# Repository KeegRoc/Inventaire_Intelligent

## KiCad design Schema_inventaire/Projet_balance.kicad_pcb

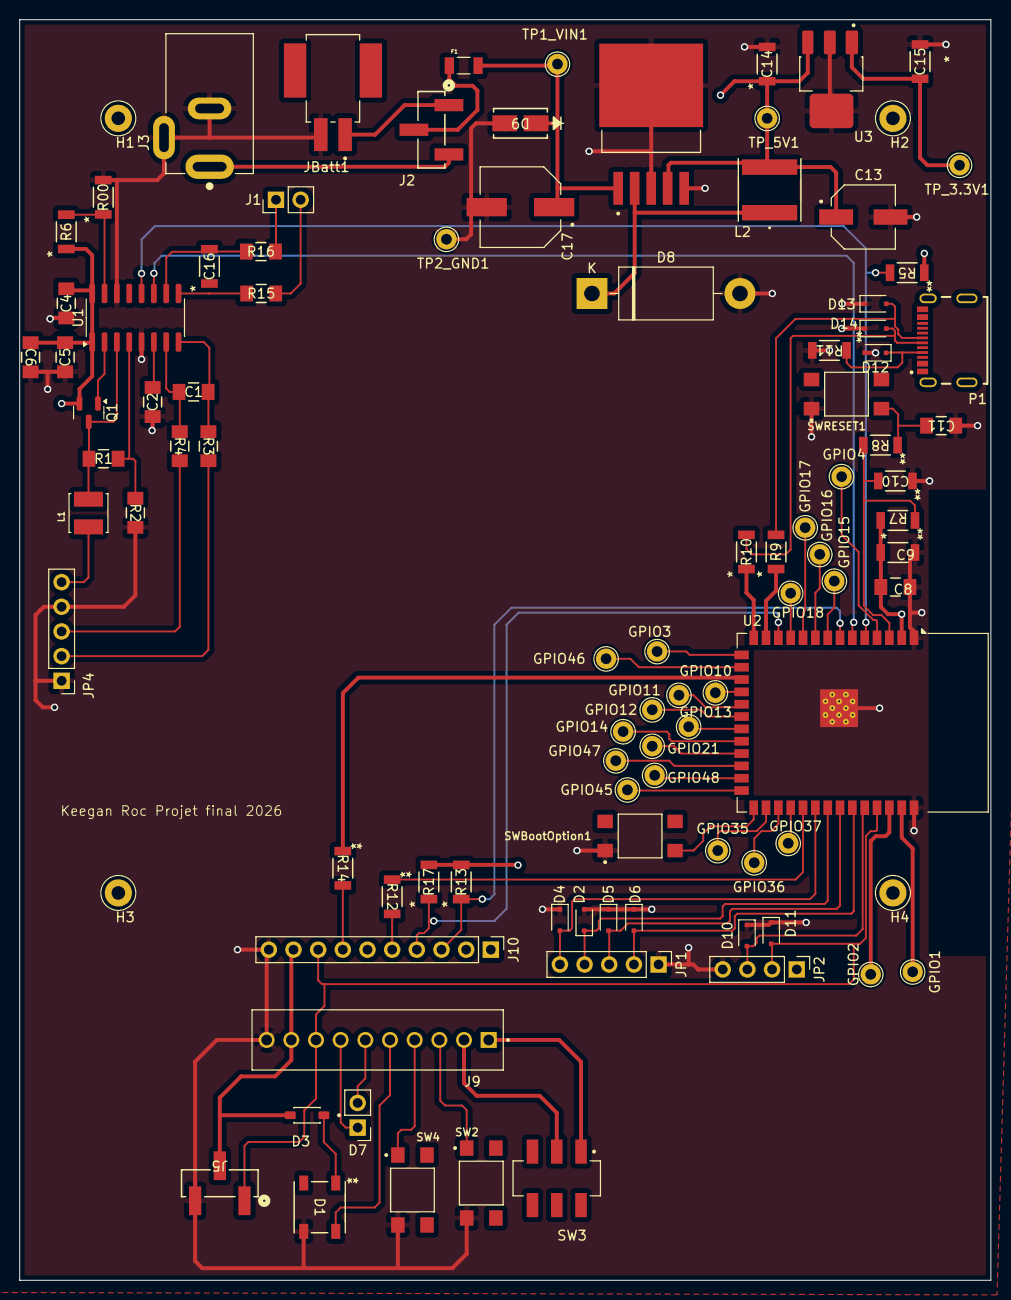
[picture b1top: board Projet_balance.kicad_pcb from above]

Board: 4 copper layers, 100.0 x 129.8 mm, 99 parts (0 on the bottom side), 73 nets.

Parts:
C1, C2, C4, C5, C8, C11: 0.1uF; RC1206N_YAG-M
C6: 10uF; RC1206N_YAG-M
C9: 22uF; 1206LSeries_LTF-M
C10, C14: 1uF; 1206LSeries_LTF-M
C13: 220uF; CAP_16SVPK220M
C15: 4.7uF; 1206LSeries_LTF-M
C16: 0.1uF; 1206LSeries_LTF-M
C17: 680uF; CAP_16SVPK680M
D1: WS2812B; COM-16347_SPK-M
D2, D4, D5, D6, D10, D11, D12, D13, D14: Diode_SMD:D_SOD-323F; D_SOD-323F
D3: 1N4148; SOD3716X135N
D7: LED_SET; PinHeader_1x02_P2.54mm_Vertical
D8: 1N5824; D_DO-201AD_P15.24mm_Horizontal
D9: PTVS5V0Z1USK; SMASeries_LTF-M
F1: Fuse; Resistance 1206
GPIO1, GPIO2, GPIO3, GPIO4, GPIO10, GPIO11, GPIO12, GPIO13, GPIO14, GPIO15, GPIO16, GPIO17, GPIO18, GPIO21, GPIO35, GPIO36, GPIO37, GPIO45, GPIO46, GPIO47, GPIO48: TestPoint; test_point_proto2
H1, H2, H3, H4: MountingHole_Pad_MP; TestPoint_Loop_D3.50mm_Drill1.4mm_Beaded
J1: Conn_01x02; PinHeader_1x02_P2.54mm_Vertical
J2: Jumper; CONN03_87898_M-5p84_MOL
J3: Power jack 9V; CUI_PJ-002A
J5: LCD; CONN03_87898_M-5p84_MOL
J9: Conn_01x10; PHOENIX_1725737
J10: Conn_01x10; PinHeader_1x10_P2.54mm_Vertical
JBatt1: Batt; PHOENIX_1702473
JP1: JTAG; PinHeader_1x05_P2.54mm_Vertical
JP2: UART; PinHeader_1x04_P2.54mm_Vertical
JP4: Conn_01x05; PinHeader_1x05_P2.54mm_Vertical
L1: 3.3uH; IND_LQH44PN3R3MP0K
L2: 33uH; IND_TAIYO_NRS6028_TAY
P1: USB_C_Plug_USB2.0; GCT_USB4215-03-A_REVA
Q1: MMBTA56; SOT-23
R00, R8, R9, R10: 0; 1206LSeries_LTF-M
R1: 20k; RC1206N_YAG-M
R2: 8.2k; RC1206N_YAG-M
R3, R4, R15, R16: 100; RC1206N_YAG-M
R5: 4.7k; 1206LSeries_LTF-M
R6, R7, R13, R17: 10k; 1206LSeries_LTF-M
R11: 5.1k; 1206LSeries_LTF-M
R12: 22; 1206LSeries_LTF-M
R14: 220; 1206LSeries_LTF-M
SW2: SW_SEL; SW_TL3305AF260QG
SW3: On/Off; SW_JS202011SCQN
SW4: SW_OPT; SW_TL3305AF260QG
SWBootOption1: SW_Push; SW_TL3305AF260QG
SWRESET1: SW_Push; SW_TL3305AF260QG
TP1_VIN1, TP2_GND1: TestPoint; test_point_proto2
TP_3.3V1, TP_5V1: TestPoint; test_point_proto2
U1: HX711; SOP-16_3.9x9.9mm_P1.27mm
U2: ESP32-S3-WROOM-1
U3: LDL1117S33R; SOT230P700X180-4N
U5: LM2575-5.0BU; VREG_TPS79625KTTR

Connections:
5V: C13.1, C14.1, D3.2 (A), J5.2, J9.9, J10.6, J10.9, L2.2, U3.3 (VI), U5.4 (FB)
+3.3V: C4.2, C5.2, C6.1, C8.1, C9.1, C15.1, JP2.1, Q1.2 (E), R5.1, R6.1, R7.2, R13.2, R17.2, TP_3.3V1.1, U1.1 (VSUP), U1.16 (DVDD), U2.2 (3V3), U3.1 (VO)
/Microcontrôleur/EN: C10.2, R7.1, R8.2, U2.3 (EN)
/Microcontrôleur/I0O: SWBootOption1.2, U2.27 (IO0)
/Microcontrôleur/LED_ON-: R14.1, U2.17 (IO9)
/Microcontrôleur/LED_RGB_IN: R12.1, U2.31 (IO38)
/Microcontrôleur/SW_OPT: J10.4, R17.1, U2.12 (IO8)
/Microcontrôleur/SW_SEL+: J10.3, R13.1, U2.7 (IO7)
/Microcontrôleur/TCK: D2.2 (A2), JP1.5, U2.32 (IO39)
/Microcontrôleur/TDI: D5.2 (A2), JP1.3, U2.34 (IO41)
/Microcontrôleur/TDO: D4.1 (A1), JP1.4, U2.33 (IO40)
/Microcontrôleur/TMS: D6.2 (A2), JP1.2, U2.35 (IO42)
/Microcontrôleur/USB_D+: D14.2 (A2), P1.A6 (D+), R10.2
/Poid/A+: JP4.2 (A+), R3.2
/Poid/A-: JP4.3 (A-), R4.2
/Utilisateur/BATT+: J9.1, SW3.1 (A)
/Utilisateur/LED_ON+: D7.2 (A), J9.6
/Utilisateur/LED_ON-: D7.1 (K), J9.7
/Utilisateur/LED_RGB_IN: D1.4 (DIN), J9.5
/Utilisateur/POWER_IN: J9.2, SW3.2 (B)
/Utilisateur/SW_OPT: J9.4, SW4.1
/Utilisateur/SW_SEL+: J9.3, SW2.1
ESP_TX: D11.2 (A2), J5.1, J9.8, J10.8, JP2.2, U2.37 (TXD0)
GND: C2.1, C4.1, C5.1, C6.2, C8.2, C9.2, C10.1, C11.1, C13.2, C14.2, C15.2, C17.2, D1.3 (VSS), D2.1 (A1), D4.2 (A2), D5.1 (A1), D6.1 (A1), D8.2 (A), D9.2 (A), D10.1 (A1), D11.1 (A1), D12.2 (A2), D13.1 (A1), D14.1 (A1), J3.2, J3.3, J5.3, J9.10, J10.10, JBatt1.2, JP1.1, JP2.4, JP4.1 (Shield), JP4.4 (E-), R00.2, R2.2, R11.2, SW2.2, SW4.2, SWBootOption1.1, SWRESET1.1, TP2_GND1.1, U1.5 (AGND), U1.14 (XI), U2.1 (GND), U2.40 (GND), U2.41 (GND), U3.2 (GND), U3.4, U5.3 (GND), U5.5 (~ON/OFF), U5.6
HX711_DOUT: R5.2, U1.12 (DOUT), U2.5 (IO5)
HX711_SCK: U1.11 (PD_SCK), U2.6 (IO6)
unnamed: C11.2, R8.1, SWRESET1.2
unnamed: D1.1 (VDD), D3.1 (K)
unnamed: D8.1 (K), L2.1, U5.2 (OUT)
unnamed: C17.1, D9.1 (K), F1.2, TP1_VIN1.1, U5.1 (VIN)
unnamed: D10.2 (A2), JP2.3, U2.36 (RXD0)
unnamed: D12.1 (A1), P1.A5 (CC), R11.1
unnamed: D13.2 (A2), P1.A7 (D-), R9.2
unnamed: J1.1, R16.2
unnamed: J1.2, R15.2
unnamed: J2.1, JBatt1.1
unnamed: F1.1, J2.2
unnamed: J2.3, J3.1
unnamed: J10.5, R12.2
unnamed: J10.7, R14.2
unnamed: JP4.5 (E+), L1.1
unnamed: Q1.1 (B), U1.2 (BASE)
unnamed: L1.2, Q1.3 (C), R1.1, U1.3 (AVDD)
unnamed: C1.2, R3.1, U1.8 (INA+)
unnamed: C1.1, R4.1, U1.7 (INA-)
unnamed: C16.2, R16.1, U1.10 (INB+)
unnamed: C16.1, R15.1, U1.9 (INB-)
unnamed: R00.1, R6.2, U1.15 (RATE)
unnamed: C2.2, U1.6 (VBG)
unnamed: R1.2, R2.1, U1.4 (VFB)
unnamed: GPIO1.1, U2.39 (IO1)
unnamed: GPIO2.1, U2.38 (IO2)
unnamed: GPIO3.1, U2.15 (IO3)
unnamed: GPIO4.1, U2.4 (IO4)
unnamed: GPIO10.1, U2.18 (IO10)
unnamed: GPIO11.1, U2.19 (IO11)
unnamed: GPIO12.1, U2.20 (IO12)
unnamed: GPIO13.1, U2.21 (IO13)
unnamed: GPIO14.1, U2.22 (IO14)
unnamed: GPIO15.1, U2.8 (IO15)
unnamed: GPIO16.1, U2.9 (IO16)
unnamed: GPIO17.1, U2.10 (IO17)
unnamed: GPIO18.1, U2.11 (IO18)
unnamed: GPIO21.1, U2.23 (IO21)
unnamed: GPIO35.1, U2.28 (IO35)
unnamed: GPIO36.1, U2.29 (IO36)
unnamed: GPIO37.1, U2.30 (IO37)
unnamed: GPIO45.1, U2.26 (IO45)
unnamed: GPIO46.1, U2.16 (IO46)
unnamed: GPIO47.1, U2.24 (IO47)
unnamed: GPIO48.1, U2.25 (IO48)
unnamed: R10.1, U2.14 (USB_D+)
unnamed: R9.1, U2.13 (USB_D-)

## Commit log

2026-06-10 ajout boitier 3d, firmware et schéma électrique
2026-06-10 ajout du code source
